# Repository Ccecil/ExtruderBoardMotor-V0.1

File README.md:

# ExtruderBoardMotor-V0.1
Extruder harness board for 3d printers

Key features:

Single common +V wire which powers hotend, fans and other outputs
5v line with optional output
Probe input with servo header 
Motor connector with multiple connector options
XT30 Connector for Hotend allows easy swap.
Locking JST connectors for fans and hotend sensor.

Assembled units available at https://www.robosprout.com/product/extruderboard-with-harness-assembled/

When I produce this board I use 2oz copper.  I have not tested 1oz yet.

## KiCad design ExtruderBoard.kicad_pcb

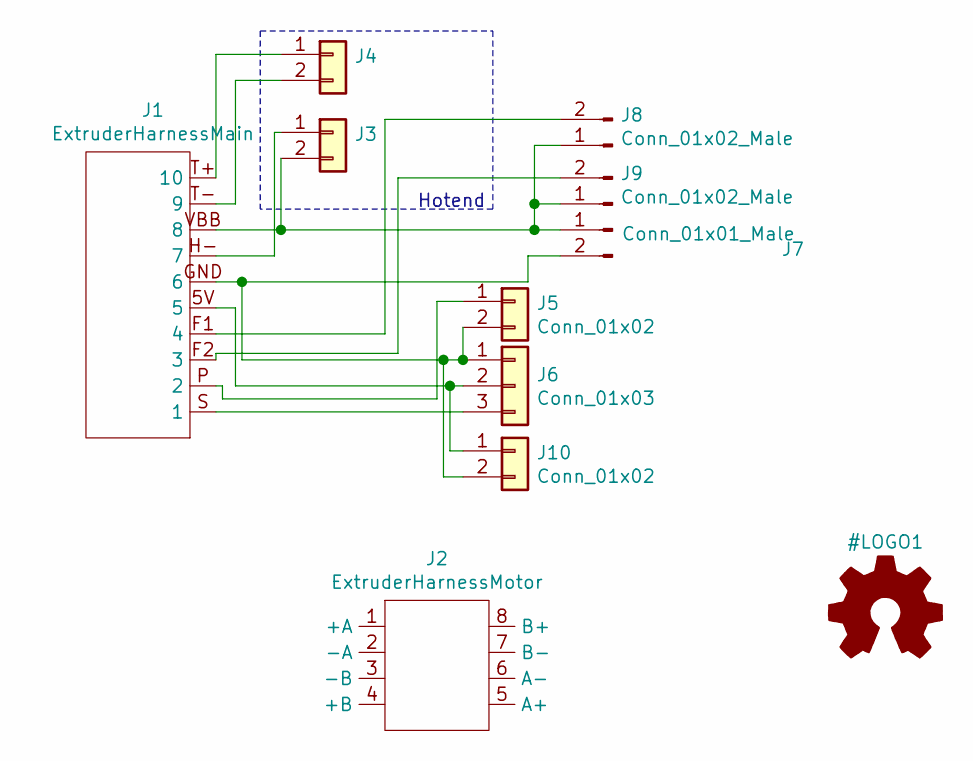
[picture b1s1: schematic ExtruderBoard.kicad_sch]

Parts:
J1: ExtruderHarnessMain; ExtruderHarnessWire
J2: ExtruderHarnessMotor; MotorPlugHarness
J3: Conn_01x02; AMASS_XT30PW-F_1x02_P2.50mm_Horizontal
J4: Conn_01x02; JST_EH_S2B-EH_1x02_P2.50mm_Horizontal
J5, J10: Conn_01x02; Molex_KK-254_AE-6410-02A_1x02_P2.54mm_Vertical
J6: Conn_01x03; Molex_KK-254_AE-6410-03A_1x03_P2.54mm_Vertical
J7: Conn_01x01_Male; Molex_KK-254_AE-6410-02A_1x02_P2.54mm_Vertical
J8, J9: Conn_01x02_Male; JST_XH_B2B-XH-A_1x02_P2.50mm_Vertical

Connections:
unnamed: J1.5V (5), J6.2, J10.1
unnamed: J1.F1 (4), J8.2
unnamed: J1.F2 (3), J9.2
unnamed: J1.GND (6), J5.2, J6.1, J7.2, J10.2
unnamed: J1.H- (7), J3.1
unnamed: J1.P (2), J5.1
unnamed: J1.S (1), J6.3
unnamed: J1.T+ (10), J4.1
unnamed: J1.T- (9), J4.2
unnamed: J1.VBB (8), J3.2, J7.1, J8.1, J9.1

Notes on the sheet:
Hotend

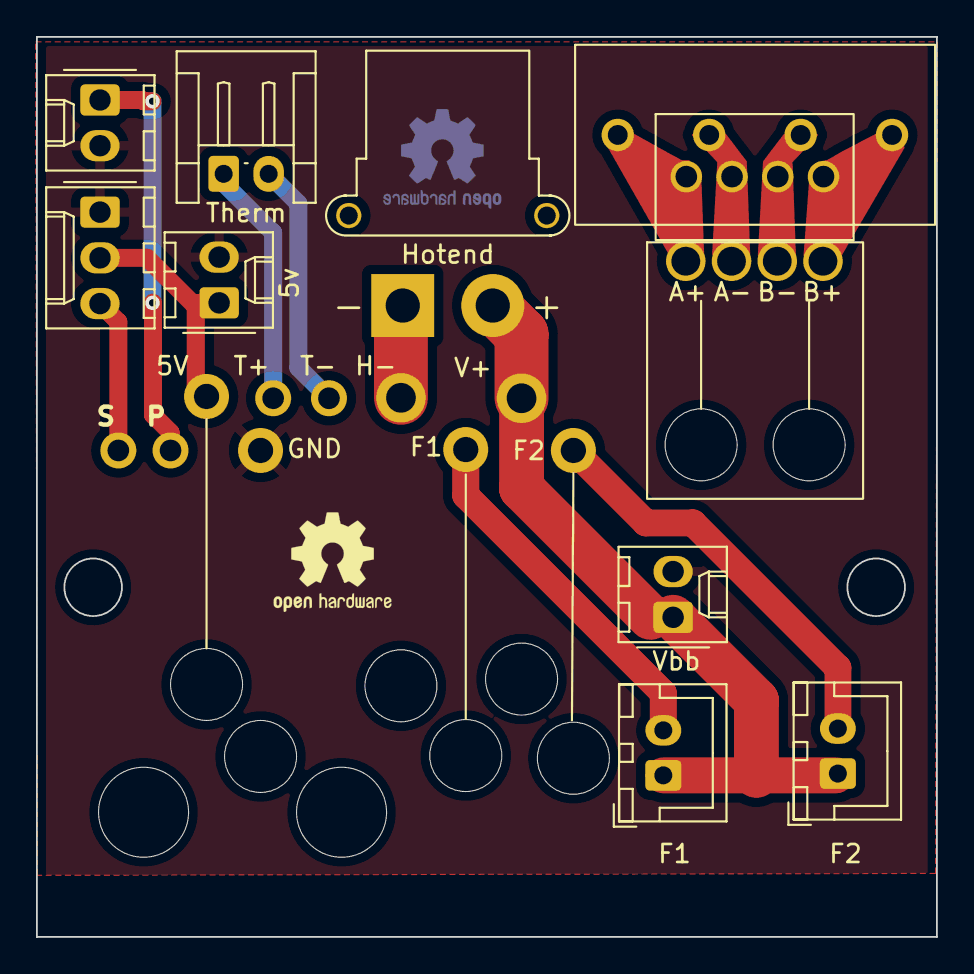
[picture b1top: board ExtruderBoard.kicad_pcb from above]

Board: 2 copper layers, 50.0 x 50.0 mm, 10 parts (0 on the bottom side), 10 nets.
